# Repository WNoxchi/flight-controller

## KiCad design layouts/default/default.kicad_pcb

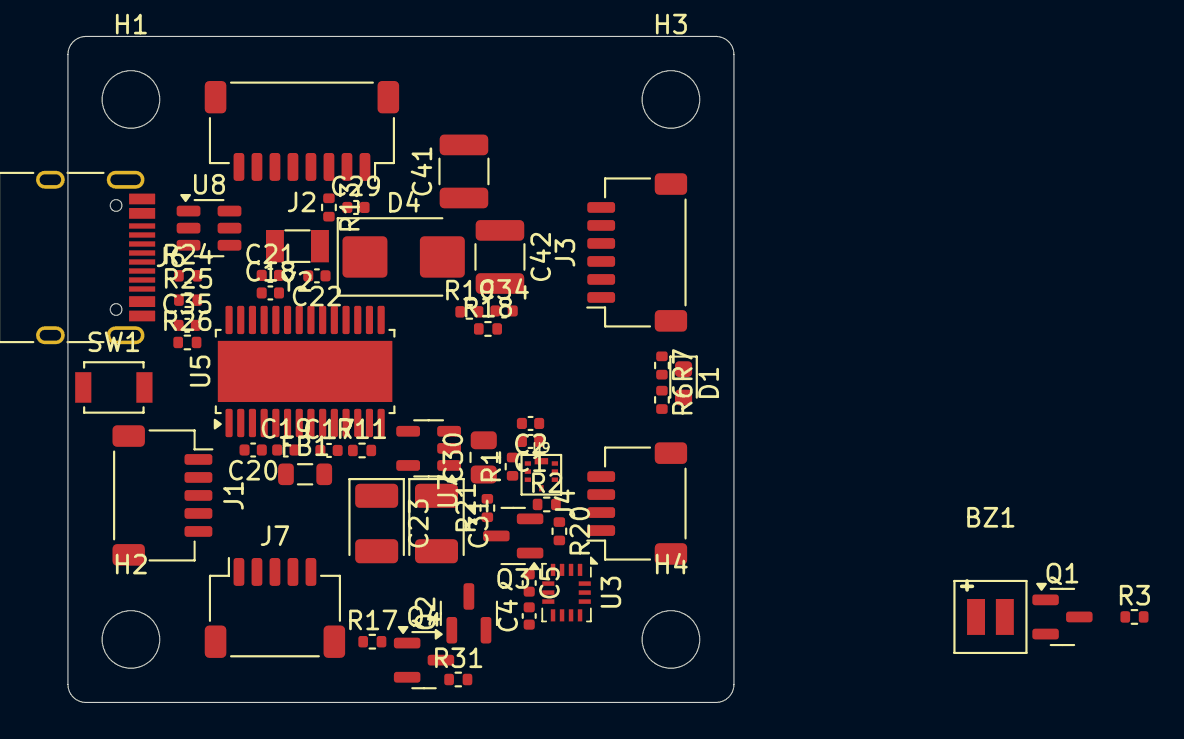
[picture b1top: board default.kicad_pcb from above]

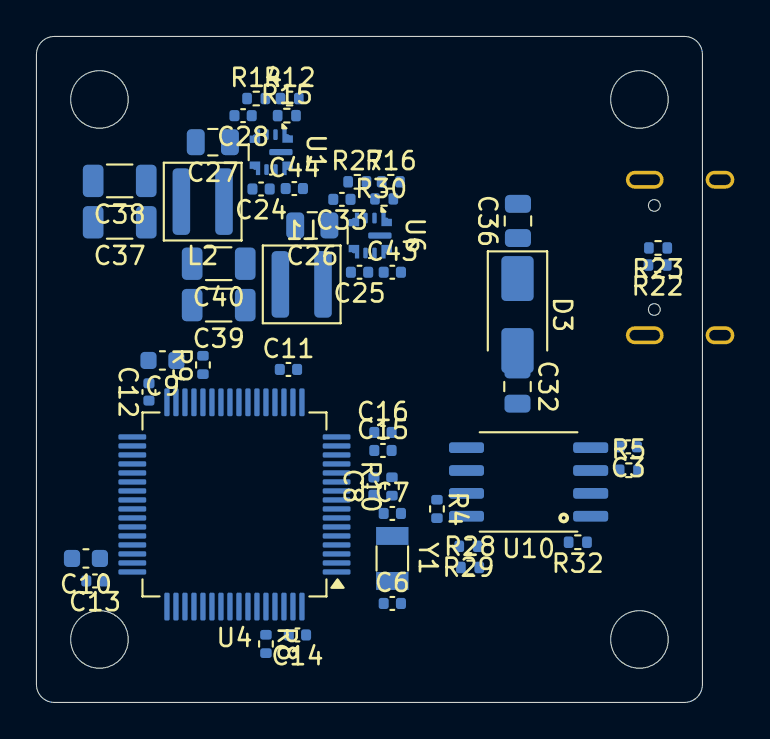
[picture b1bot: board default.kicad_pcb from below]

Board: 2 copper layers, 37.0 x 37.0 mm, 109 parts (50 on the bottom side), 83 nets, no tracks yet.

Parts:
BZ1: Buzzer_SMD_CMT-4023S_4x4mm
C1, C2, C3, C4, C5, C6, C7, C8, C11, C12, C13, C14, C15, C16, C17, C18, C19, C20, C21, C22, C24, C25, C28, C29, C33, C34, C35, C43, C44: C_0402_1005Metric
C9, C10: C_0603_1608Metric
C23, C31: CP_EIA-3528-21_Kemet-B
C26, C27, C30, C32, C36: C_0805_2012Metric
C37, C38, C39, C40: C_1206_3216Metric
C41, C42: C_1210_3225Metric
D1: LED_0603_1608Metric
D3: D_SMA
D4: D_SMB
FB1: L_0805_2012Metric
H1, H2, H3, H4: MountingHole_3.2mm_M3
J1, J7: JST_SH_SM05B-SRSS-TB_1x05-1MP_P1.00mm_Horizontal
J2: JST_SH_SM08B-SRSS-TB_1x08-1MP_P1.00mm_Horizontal
J3: JST_SH_SM06B-SRSS-TB_1x06-1MP_P1.00mm_Horizontal
J4: JST_SH_SM04B-SRSS-TB_1x04-1MP_P1.00mm_Horizontal
J6: USB_C_Receptacle_HRO_TYPE-C-31-M-12
L1, L2: L_Wuerth_MAPI-4020
Q1, Q2, Q3, Q4: SOT-23
R1, R2, R3, R4, R5, R6, R7, R8, R9, R10, R11, R12, R13, R14, R15, R16, R17, R18, R19, R20, R21, R22, R23, R24, R25, R26, R27, R28, R29, R30, R31, R32: R_0402_1005Metric
SW1: SW_SPST_B3U-1000P
U1, U6: TI_RPE0009B_VQFN-HR-9_2x2mm_P0.5mm
U3: Bosch_LGA-14_3x2.5mm_P0.5mm
U4: LQFP-64_10x10mm_P0.5mm
U5: TSSOP-28-1EP_4.4x9.7mm_P0.65mm_EP3.4x9.7mm_Mask3.1x4.05mm
U7: SOT-23-5
U8: SOT-23-6
U9: Bosch_LGA-10_2x2mm_P0.275x0.250mm
U10: SOIC-8_5.23x5.23mm_P1.27mm
Y1, Y2: Crystal_SMD_3215-2Pin_3.2x1.5mm

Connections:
A5: J6.A5, R22.1
B5: J6.B5, R23.1
adc_curr: C29.1, R13.2, U4.9
adc_vbat: C34.1, R18.1, R19.2, U4.10
anode: D1.2, R6.2
avdd: C17.1, FB1.2, U5.9
baro-gnd: C1.2, C2.2, C3.2, C4.2, C5.2, C17.2, C18.2, C19.2, C21.2, C22.2, C23.2, C26.2, C27.2, C28.2, C29.2, C30.2, C31.2, C32.2, C33.2, C34.2, C35.2, C36.2, C37.2, C38.2, C39.2, C40.2, C41.2, C42.2, C43.2, C44.2, D4.1, J1.1, J1.5, J2.1, J3.1, J4.1, J6.A1, J6.A12, J6.B1, J6.B12, J7.2, Q1.2, Q3.2, Q4.2, R12.2, R16.2, R18.2, R22.2, R23.2, R26.2, R28.2, R32.2, U1.9, U3.6, U3.7, U5.6, U5.10, U5.24, U5.29, U6.1, U6.9, U7.2, U8.3, U9.3, U9.8, U9.9, U10.4
baro-vdd: C1.1, C2.1, C3.1, C4.1, C5.1, C11.1, C12.1, C13.1, C14.1, C15.1, C16.1, C18.1, C19.1, C23.1, C31.1, FB1.1, R1.2, R2.2, R4.2, R5.2, R6.1, R10.2, R11.2, R21.2, SW1.2, U3.5, U3.8, U4.1, U4.13, U4.19, U4.32, U4.48, U4.64, U5.5, U5.25, U7.5, U9.1, U9.5, U9.6, U9.10, U10.8
beeper-drain: BZ1.2, Q1.3
beeper-gate: Q1.1, R3.2
beeper-gpio: R3.1, U4.27
beeper-vdd: BZ1.1, C30.1, C32.1, C39.1, C40.1, D3.2, J1.2, J3.2, J4.2, L1.2, R30.2, U6.8, U7.1, U7.3
boot0: R8.1, SW1.1, U4.60
buck-boot: C25.1, U6.6
buck-en: R16.1, R27.2, U6.3
buck-pgood: R30.1, U6.2
buck-sw: C25.2, L1.1, U6.5
buck-vcc: C43.1, U6.7
buck_vtx-boot: C24.1, U1.6
buck_vtx-en: R12.1, R14.2, U1.3
buck_vtx-pgood: R15.1, U1.2
buck_vtx-sw: C24.2, L2.1, U1.5
buck_vtx-vcc: C44.1, U1.7
c_hse1-gnd: C6.2, C7.2, C8.2, C9.2, C10.2, C11.2, C12.2, C13.2, C14.2, C15.2, C16.2, R8.2, R9.2, U4.12, U4.18, U4.63
c_sag-video_in: C20.2, J7.3, U5.3
cam_conn-video_in: J1.3, U5.8
cam_ctrl: J1.4, U4.55
clkin: C21.1, U5.23, Y2.1
conn-rx-0: J3.4, U4.17
conn-rx-1: J4.3, R20.1
conn-tx-0: J3.3, U4.16
conn-tx-1: J4.4, U4.42
conn-uart_rx: J7.4, U4.54
conn_dm: J6.A7, J6.B7, R24.1, U8.1, U8.2
conn_dp: J6.A6, J6.B6, R25.1, U8.5, U8.6
curr: J2.3, R13.1
data: R7.1, U4.58
dm: R24.2, U4.44
dp: R25.2, U4.45
exti: U3.4, U4.25
fb: R28.1, R29.2, U1.8
flash-cs: U4.59, U10.1
flash-spi_miso: U4.52, U10.2
flash-spi_mosi: U4.57, U10.5
flash-spi_sck: U4.51, U10.6
footprint-cs-0: U3.12, U4.24
footprint-cs-1: U4.33, U5.20
footprint-drain: Q2.1, Q4.3, R31.1
footprint-gate-0: Q4.1, R17.2
footprint-gate-1: Q3.1, R20.2
footprint-gpio-0: D1.1, U4.26
footprint-spi_miso-0: U3.1, U4.22
footprint-spi_miso-1: U4.35, U5.17
footprint-spi_mosi-0: U3.14, U4.23
footprint-spi_mosi-1: U4.36, U5.19
footprint-spi_sck-0: U3.13, U4.21
footprint-spi_sck-1: U4.34, U5.18
footprint-uart_rx: Q3.3, R21.1, U4.43
hold: R4.1, U10.7
nrst: C8.1, R10.1, U4.7
pb2: R9.1, R17.1, U4.28
pc6: J2.4, U4.37
pc7: J2.5, U4.38
pc8: J2.6, U4.39
pc9: J2.7, U4.40
rail_10v_vtx: C37.1, C38.1, L2.2, Q2.2, R15.2, R29.1, R31.2
reset: R11.1, U5.11
rt: R32.1, U1.1
sag: C20.1, U5.4
scl: J3.5, R1.1, U4.61, U9.2
sda: J3.6, R2.1, U4.62, U9.4
shield: C35.1, J6.S1, R26.1
telem: J2.8, U4.15
uart_tx: J7.5, U4.53
vbat: C26.1, C27.1, C28.1, C33.1, C41.1, C42.1, D4.2, J2.2, R14.1, R19.1, R27.1, U1.4, U6.4
vbus: C36.1, D3.1, J6.A4, J6.A9, J6.B4, J6.B9, U8.4
vcap1: C9.1, U4.31
vcap2: C10.1, U4.47
vtx_10v: J7.1, Q2.3
wp: R5.1, U10.3
xfb: C22.1, U5.22, Y2.2
xin: C6.1, U4.5, Y1.1
xout: C7.1, U4.6, Y1.2

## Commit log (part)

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2026-03-01 initial files
2026-03-01 add assert constraints; add ato.yaml
2026-03-01 add agents.md
2026-03-01 add loop.sh
2026-03-01 add .gitignore
2026-03-01 add python env note
2026-03-01 update agents with python env
2026-03-01 initital implementation plan
2026-03-01 update loop
2026-03-02 fix typo
2026-03-02 add layout checklist guide
2026-03-03 update build prompt
